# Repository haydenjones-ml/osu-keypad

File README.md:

Design files for Keypad (Kicad, gerber)

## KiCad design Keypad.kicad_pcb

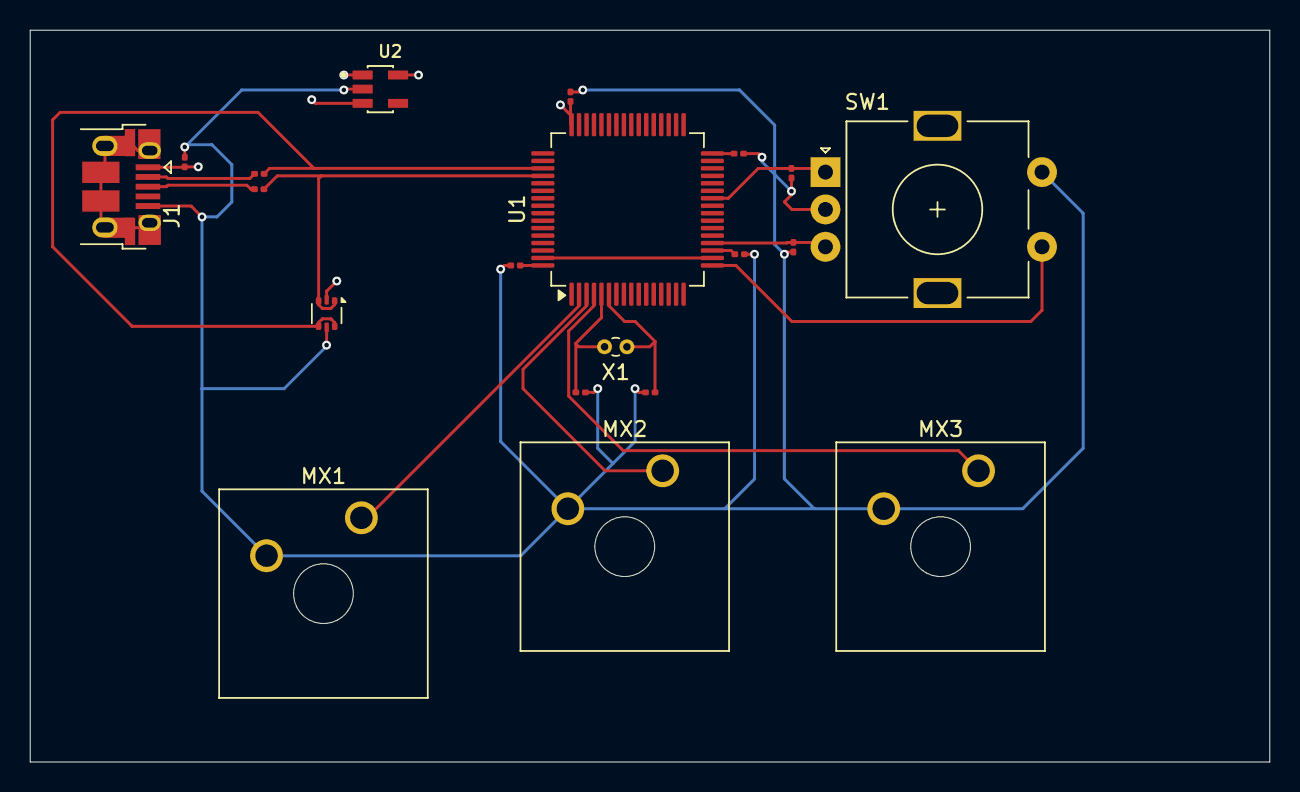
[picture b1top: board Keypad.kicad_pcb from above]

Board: 4 copper layers, 83.0 x 49.0 mm, 20 parts (0 on the bottom side), 18 nets.

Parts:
C1, C9: C; C_0201_0603Metric
C2: 0.1 µF (each); C_0201_0603Metric
C3, C4, C5: C_0201_0603Metric
C6, C7: 20 pF; C_0201_0603Metric
C8: 0.1 µF; C_0201_0603Metric
J1: USB_B_Micro; USB_Micro-B_Amphenol_10103594-0001LF_Horizontal
MX1, MX2, MX3: MX-NoLED; SW_Cherry_MX_1.75u_Plate
R1, R2: 220 Ω; R_0201_0603Metric
SW1: RotaryEncoder_Switch; RotaryEncoder_Alps_EC11E-Switch_Vertical_H20mm
U1: STM32F205RBTx; LQFP-64_10x10mm_P0.5mm
U2: AP2112K-3.3TRG1; SOT95P285X140-5N
U3: USBLC6-2P6; SOT-666
X1: 8 MHz; Crystal_DS10_D1.0mm_L4.3mm_Vertical

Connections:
/D+: J1.3 (D+), R1.1
/D-: J1.2 (D-), R2.1
GND: C1.1, C2.1, C3.1, C4.1, C5.1, C6.2, C7.1, C8.1, C9.2, J1.5 (GND), MX1.2 (ROW), MX2.2 (ROW), MX3.2 (ROW), SW1.C, SW1.S2, U2.2 (GND), U3.5 (VBUS)
unnamed: C2.2, U1.64 (VDD)
unnamed: C4.2, U1.32 (VDD)
unnamed: C5.2, U1.19 (VDD)
unnamed: MX1.1 (COL), U1.2 (PC13)
unnamed: MX2.1 (COL), U1.3 (PC14)
unnamed: MX3.1 (COL), U1.4 (PC15)
unnamed: SW1.S1, U1.17 (PA3)
unnamed: C9.1, SW1.B, U1.20 (PA4)
unnamed: C8.2, SW1.A, U1.26 (PB0)
unnamed: R2.2, U1.51 (PC10), U3.4 (I/O2), U3.6 (I/O1)
unnamed: R1.2, U1.52 (PC11), U3.1 (I/O1), U3.3 (I/O2)
unnamed: C6.1, U1.5 (PH0), X1.2
unnamed: C7.2, U1.6 (PH1), X1.1
unnamed: U1.18 (VSS), U1.63 (VSS)
VDD: C1.2, C3.2, J1.1 (VBUS), U1.48 (VDD), U2.1 (VIN), U2.3 (EN), U2.5 (VOUT), U3.2 (GND)

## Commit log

2026-01-01 Push design files for keypad project
